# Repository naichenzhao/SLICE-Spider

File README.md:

# Spider Bot for SLICE

something something, torque controlled robot spider

## Manufacturing
- SLS_Leg_Lower and SLS_Lever_Lower can be laser cut out of acrylic
- Everything else should be 3D printed

## BOM

Parts needed per spider
- 8x 12V DC Motor: https://www.pololu.com/product/3046
- 8x Enoder for motor: https://www.pololu.com/product/4761
- 8x M3 Motor hub w/ M3 screws: https://www.pololu.com/product/1996
- 8x Homing switches for the legs: https://www.amazon.com/Cylewet-25Pcs-Switch-Arduino-CYT1073/dp/B073TYWX86/ref=sr_1_6?keywords=limit+switch&qid=1695682041&sr=8-6
- 12x M3 flanged bearing for joints: https://www.amazon.com/uxcell-Flanged-3x6x2-5mm-Shielded-Bearings/dp/B08H27NJ5N/ref=sr_1_4?keywords=M3+bearing&qid=1695672434&s=industrial&sr=1-4
- 16x M2 threaded heat insert: https://www.mcmaster.com/94180A307/

- Assortment of M2 and M3 screws/nuts

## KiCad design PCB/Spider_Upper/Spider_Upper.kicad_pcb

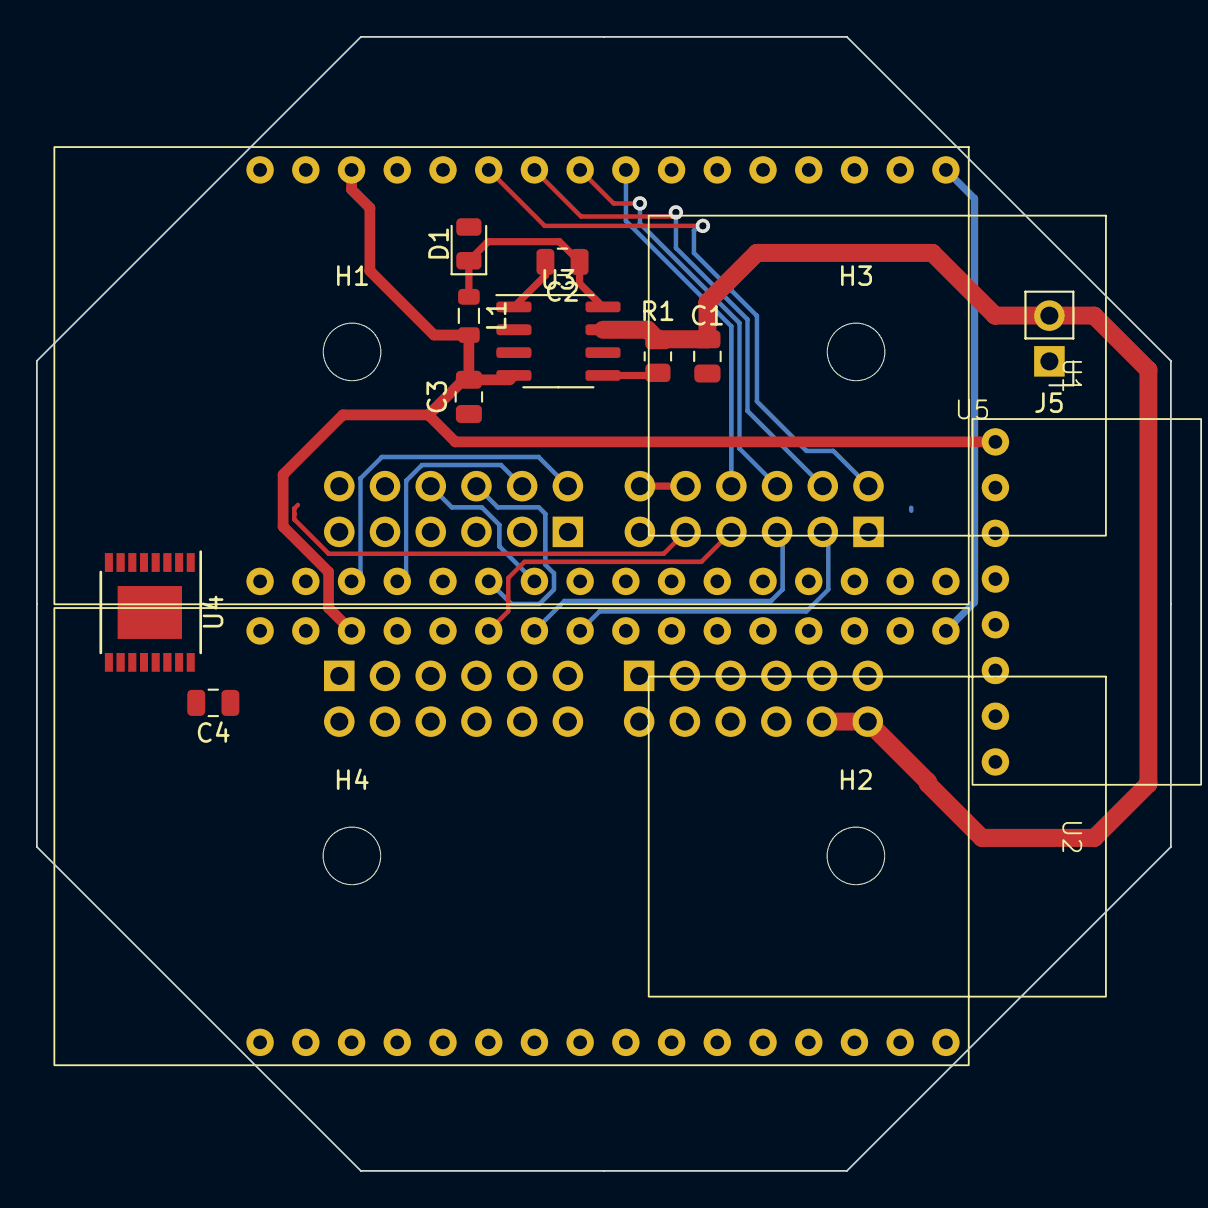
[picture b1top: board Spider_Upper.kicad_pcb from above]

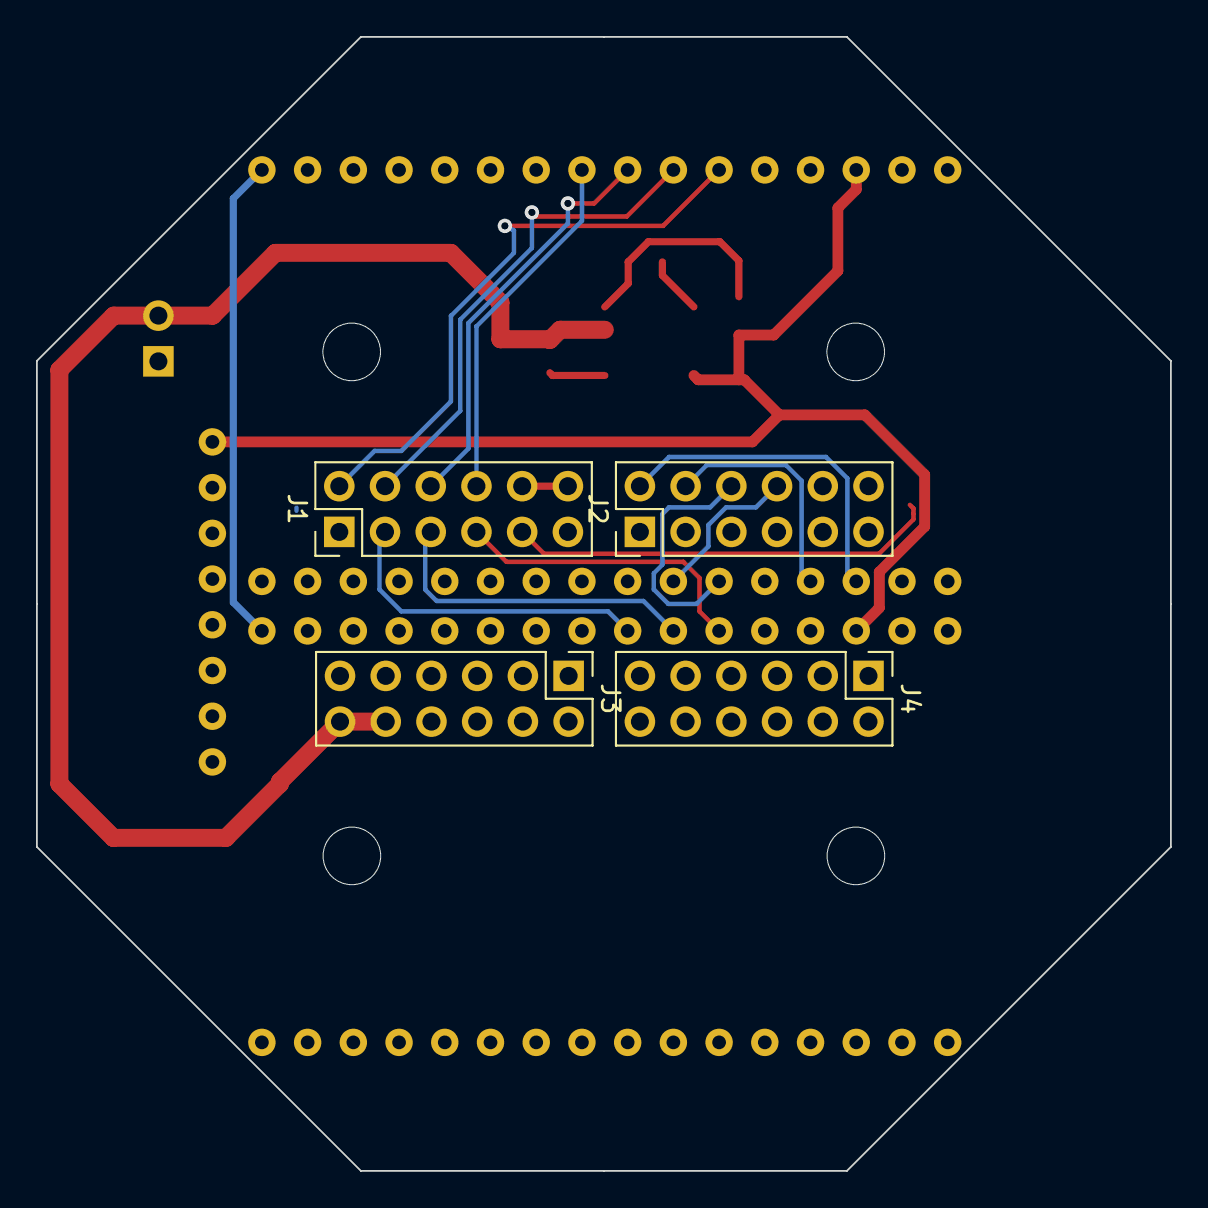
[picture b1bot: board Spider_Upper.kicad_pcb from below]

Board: 2 copper layers, 63.0 x 63.0 mm, 21 parts (4 on the bottom side), 53 nets.

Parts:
C1: 100uF; C_0805_2012Metric
C2: 10nF; C_0805_2012Metric
C3: 68uF; C_0805_2012Metric
C4: 10uF; C_0805_2012Metric
D1: D; D_0805_2012Metric
H1, H2, H3, H4: MountingHole; MountingHole_3.2mm_M3
J1, J2, J3, J4: Conn_02x06_Odd_Even; PinHeader_2x06_P2.54mm_Vertical
J5: Conn_01x02; PinHeader_1x02_P2.54mm_Vertical
L1: 47uH; L_0805_2012Metric
R1: 5k; R_0805_2012Metric
U1, U2: ESP32-C6
U3: LM2675M-5; SOIC-8_3.9x4.9mm_P1.27mm
U4: TSSOP-16-1EP_4.4x5mm_P0.65mm
U5: BNO055

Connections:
+3.3V: J1.10, J1.12, U1.3V3, U2.3V3
+5V: C3.1, C4.2, L1.2, U1.5V, U2.5V, U3.4 (FB), U4.16 (VDD), U5.VIN
+12V: C1.1, J3.10, J3.12, J5.2, R1.1, U3.7 (VIN)
/EA_00: J1.2, U1.GPIO11
/EA_01: J1.6, U1.GPIO8
/EA_10: J3.2, U1.GPIO0
/EA_11: J3.6, U1.GPIO6
/EA_20: J2.2, U1.GPIO12
/EA_21: J2.6, U1.GPIO9
/EA_30: J4.2, U1.GPIO19
/EA_31: J4.6, U1.GPIO21
/EB_00: J1.4, U1.GPIO10
/EB_01: J1.8, U1.GPIO1
/EB_10: J3.4, U1.GPIO7
/EB_11: J3.8, U1.GPIO5
/EB_20: J2.4, U1.GPIO13
/EB_21: J2.8, U1.GPIO18
/EB_30: J4.4, U1.GPIO20
/EB_31: J4.8, U1.GPIO22
/GPIO15: U2.GPIO15, U4.10 (A1)
/GPIO17: U2.GPIO17, U4.9 (A2)
/GPIO22: U2.GPIO22, U4.3 (D)
/GPIO23: U2.GPIO23, U4.11 (A0)
/INA_00: J1.1, U2.GPIO1
/INA_01: J1.5, U2.GPIO10
/INA_10: J3.1, U2.GPIO5
/INA_11: J3.5, U2.GPIO7
/INA_20: J2.1, U2.GPIO12
/INA_21: J2.5, U2.GPIO9
/INA_30: J4.1, U2.GPIO18
/INA_31: J4.5, U2.GPIO20
/INB_00: J1.3, U2.GPIO8
/INB_01: J1.7, U2.GPIO11
/INB_10: J3.3, U2.GPIO6
/INB_11: J3.7, U2.GPIO0
/INB_20: J2.3, U2.GPIO13
/INB_21: J2.7, U2.GPIO4
/INB_30: J4.3, U2.GPIO19
/INB_31: J4.7, U2.GPIO21
/SCL: U1.GPIO2, U2.GPIO2, U5.SCL
/SDA: U1.GPIO3, U2.GPIO3, U5.SDA
/SW_00: J1.9, U4.13 (S0)
/SW_01: J1.11, U4.14 (S1)
/SW_10: J3.9, U4.15 (S2)
/SW_11: J3.11, U4.12 (S3)
/SW_20: J2.9, U4.1 (S4)
/SW_21: J2.11, U4.5 (S5)
/SW_30: J4.9, U4.2 (S6)
/SW_31: J4.11, U4.4 (S7)
GND: C1.2, C3.2, C4.1, D1.2 (A), J2.10, J2.12, J4.10, J4.12, J5.1, U1.GND, U2.GND, U3.6 (GND), U4.6 (NOT_EN), U4.7 (VSS), U4.8 (GND), U5.GND
unnamed: C2.1, D1.1 (K), L1.1, U3.8 (VSW)
unnamed: C2.2, U3.1 (CB)
unnamed: R1.2, U3.5 (ON/~OFF)

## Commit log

2023-09-23 initial commit stuff
2023-09-23 added images
2023-09-25 added homing switches
2023-09-25 stuff
2023-09-25 applied updates
2023-09-25 created stl/moved sld files
2023-09-25 addedc colours
2023-10-02 modified stuff
2023-10-02 updated body with more holes
2023-10-06 tried to export to urdf
2023-10-07 new URDF files
2023-10-09 updated urdf name
2023-10-14 updated URDF
2023-10-14 updated meshes
2023-10-14 testing part instead of asm
2023-10-14 updated URDF files again, hopefully for the last time
2023-10-14 testing limits
2023-10-14 manually updated URDF file for simplified sollision
2023-10-28 added testbenches
2023-11-06 some prep to export to onshape
2023-11-06 added heatset holes
2023-12-11 progress on PCBs
2023-12-13 finished V1 PCB
2023-12-16 pushing PCBs with STEP files
2023-12-29 some changes
2023-12-31 pain
2024-01-02 i2c makes me want to kill myself
2024-01-02 I actually want to kil myself
2024-01-05 added PID and cleaned up code
2024-01-08 more images
2024-01-10 added battery holder
2024-01-10 exported new URDF file
2024-01-10 ordf with joint limits
2024-01-10 updated ros to do joint visualizer
2024-02-16 bruh
